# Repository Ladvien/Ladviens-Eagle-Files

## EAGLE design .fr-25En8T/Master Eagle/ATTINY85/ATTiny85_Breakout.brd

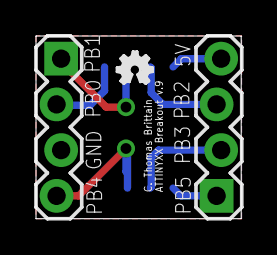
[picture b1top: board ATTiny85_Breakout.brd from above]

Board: 2 copper layers, 11.4 x 10.2 mm, 4 parts (1 on the bottom side), 8 nets.

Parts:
JP1, JP2: 1X04_LOCK
U$1: ATTINY45; SO08-EIAJ
U$2: OSHW_FILLX70_NOTEXT

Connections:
GND: JP2.3, U$1.4
PB0: JP2.2, U$1.5
PB1: JP2.1, U$1.6
PB2: JP1.3, U$1.7
PB3: JP1.2, U$1.2
PB4: JP2.4, U$1.3
PB5: JP1.1, U$1.1
VCC: JP1.4, U$1.8

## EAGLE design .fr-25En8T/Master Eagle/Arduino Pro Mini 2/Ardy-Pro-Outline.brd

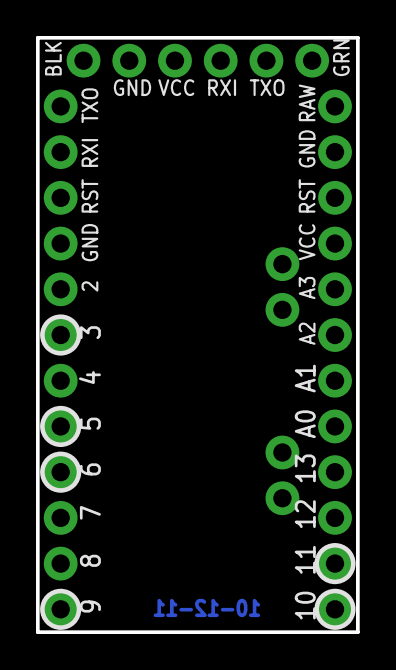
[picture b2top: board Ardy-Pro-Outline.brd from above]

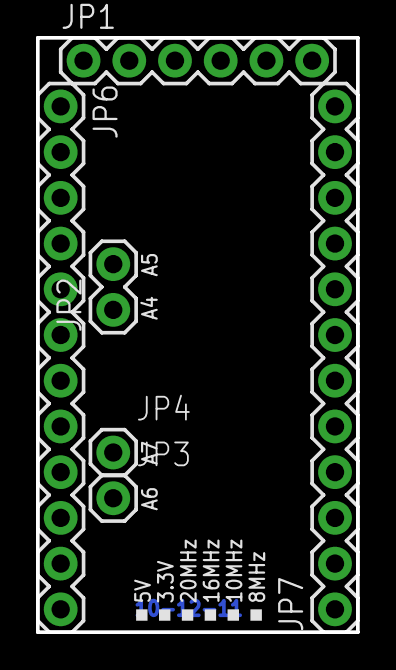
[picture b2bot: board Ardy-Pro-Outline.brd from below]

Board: 2 copper layers, 17.8 x 33.0 mm, 6 parts (6 on the bottom side), 5 nets, no tracks yet.

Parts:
JP1: FTDI Basic; 1X06
JP2: 1X02
JP3, JP4: 1X01
JP6, JP7: 1X12

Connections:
GND: JP1.5, JP1.6, JP6.2, JP7.9
RESET: JP6.3, JP7.10
RXI: JP1.3, JP7.11
TXO: JP1.2, JP7.12
VCC: JP1.4, JP6.4

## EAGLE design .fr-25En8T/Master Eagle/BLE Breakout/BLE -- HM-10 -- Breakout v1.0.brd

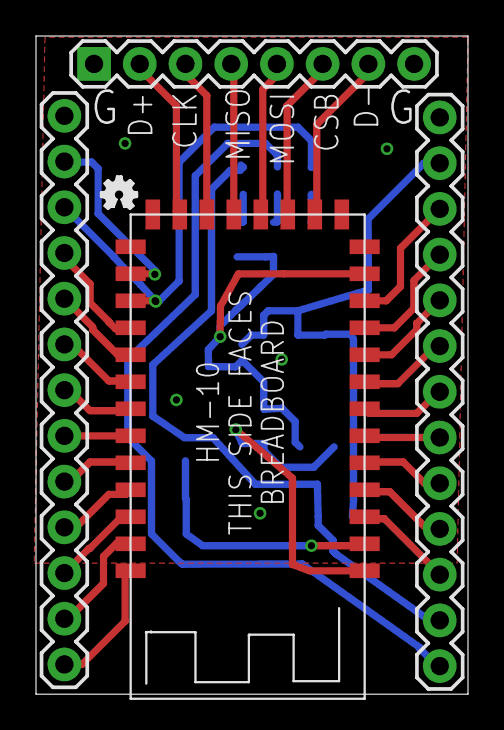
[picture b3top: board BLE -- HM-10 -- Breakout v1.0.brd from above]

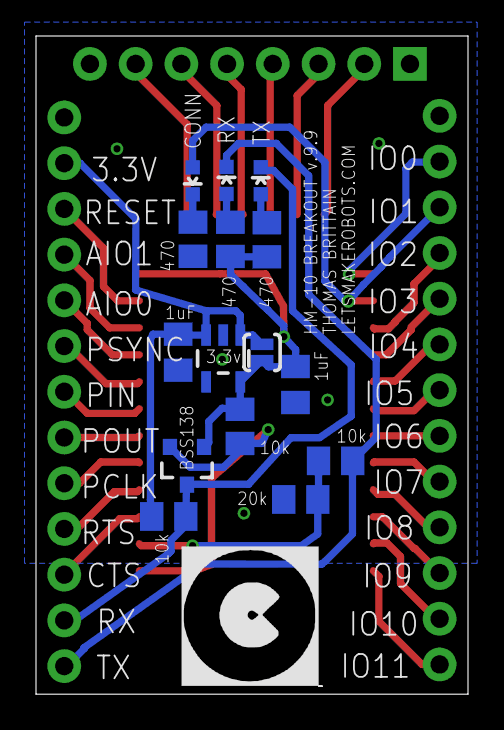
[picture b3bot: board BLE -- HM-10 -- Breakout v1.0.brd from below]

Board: 2 copper layers, 24.0 x 36.6 mm, 20 parts (15 on the bottom side), 37 nets.

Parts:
BSS138: MOSFET-NCHANNELSMD; SOT23-3
C1, C2: 1uF; C0805K
CONN_LED: LED-0603
JP1, JP2: M13; 1X13
JP3: 1X08
R1, R2: 1k; M0805
R3, R5, R6: 10k; M0805
R4: 20k; M0805
R7: 220; M0805
RX_LED: LED-0603
SJ1: SOLDERJUMPERNO; SJ_2S-NO
TX_LED: LED-0603
U1: V_REG_LDOSMD; SOT23-5
U$1: BLE-HM-10
U$3: OSHW_FILLX70_NOTEXT

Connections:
3_3V: BSS138.1, C2.1, R1.2, R2.2, R6.2, SJ1.1, U1.5, U$1.3.3V
5V: C1.1, JP1.2, R5.2, SJ1.2, U1.1, U1.3
GND: C1.2, C2.2, JP1.1, JP2.13, JP3.1, JP3.8, R4.2, R7.1, U1.2, U$1.GND1, U$1.GND2, U$1.GND3, U$1.GND4
HVTX->LVRX: R3.2, R4.1, U$1.UART_RX
LVRX->HVTX: BSS138.2, R6.1, U$1.UART_TX
unnamed: CONN_LED.A, JP2.11, U$1.PIO1
unnamed: JP1.3, U$1.RESET
unnamed: JP1.4, U$1.AIO1
unnamed: JP1.5, U$1.AIO0
unnamed: JP1.6, U$1.PCM_SYNC
unnamed: JP1.7, U$1.PCM_IN
unnamed: JP1.8, U$1.PCM_OUT
unnamed: JP1.9, U$1.PCM_CLK
unnamed: JP1.10, U$1.UART_RTS
unnamed: JP1.11, U$1.UART_CTS
unnamed: JP2.1, U$1.PIO11
unnamed: JP2.2, U$1.PIO10
unnamed: JP2.3, U$1.PIO9
unnamed: JP2.4, U$1.PIO8
unnamed: JP2.5, U$1.PIO7
unnamed: JP2.6, U$1.PIO6
unnamed: JP2.7, U$1.PIO5
unnamed: JP2.8, U$1.PIO4
unnamed: JP2.9, U$1.PIO3
unnamed: JP2.10, U$1.PIO2
unnamed: R1.1, TX_LED.A
unnamed: JP2.12, U$1.PIO0
unnamed: CONN_LED.C, R7.2
unnamed: R2.1, RX_LED.A
unnamed: JP3.2, U$1.USB_D+
unnamed: JP3.3, U$1.SPI_CLK
unnamed: JP3.4, U$1.SPI_MISO
unnamed: JP3.5, U$1.SPI_MOSI
unnamed: JP3.6, U$1.SPI_CSB
unnamed: JP3.7, U$1.USB_D-
RX: JP1.13, R3.1, RX_LED.C
TX: BSS138.3, JP1.12, R5.1, TX_LED.C

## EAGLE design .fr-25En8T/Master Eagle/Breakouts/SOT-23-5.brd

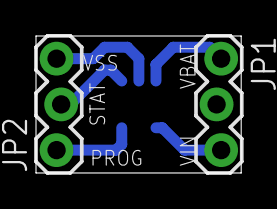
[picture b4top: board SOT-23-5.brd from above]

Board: 2 copper layers, 11.4 x 7.6 mm, 3 parts (1 on the bottom side), 5 nets.

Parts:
JP1, JP2: 1X03_LOCK
U1: MCP73831; SOT23-5

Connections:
PROG: JP2.1, U1.5
STAT: JP2.2, U1.1
VBAT: JP1.1, U1.3
VIN: JP1.3, U1.4
VSS: JP2.3, U1.2

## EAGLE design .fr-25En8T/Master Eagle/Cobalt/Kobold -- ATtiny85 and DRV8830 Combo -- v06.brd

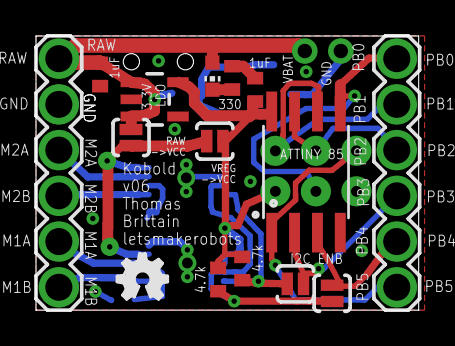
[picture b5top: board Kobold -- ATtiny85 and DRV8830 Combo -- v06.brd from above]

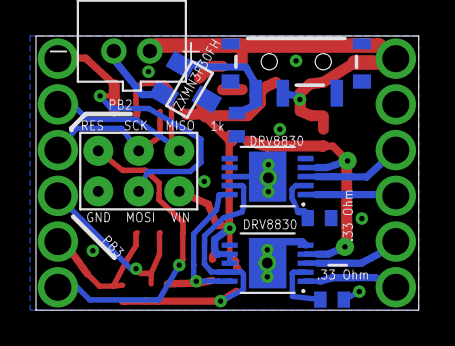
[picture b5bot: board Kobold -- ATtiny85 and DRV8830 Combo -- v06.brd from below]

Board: 2 copper layers, 21.3 x 15.2 mm, 24 parts (9 on the bottom side), 21 nets.

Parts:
1K: R3; R0402
BATTERY: JST-PH-2-THM
C1, C2: 1uf; C0402
LED1: CHIP-LED0603
R1, R3: .33; R0402
R2, R4: 1k; R0402
R5: 330; R0402
RAW: SOLDERJUMPERNO; SJ_2S-NO
S1: SWITCH-SPST-SMD-A
SJ6, SJ7: SOLDERJUMPERNO; SJ_2S-NO
U1: V_REG_LDOSMD; SOT23-5
U2, U3: DRV8830; MSOP-10-GNDPAD
U$1, U$4: 1X6_SHORT_ROUND
U$2: ATTINY85; SO08-EIAJ
U$5: POGO_PIN_SPI_PAD
U$6: OSHW_FILLX100_NOTEXT
VREG: SOLDERJUMPERNO; SJ_2S-NO
ZXMN3F30FH: MOSFET-NCHANNELBSS123LT1G; SOT23

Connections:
BAT_GND: BATTERY.2, ZXMN3F30FH.2
BAT_RAW: BATTERY.1, C1.1, LED1.A, RAW.1, S1.2, U1.1, U1.3, U$4.1
GND: C1.2, C2.2, R1.1, R3.1, R4.1, R5.2, U1.2, U2.5, U2.GND, U3.5, U3.7, U3.8, U3.GND, U$2.4, U$4.2, U$5.GND, ZXMN3F30FH.3
M1_A: U2.3, U$4.5
M1_B: U2.1, U$4.6
M2_A: U3.3, U$4.3
M2_B: U3.1, U$4.4
unnamed: R1.2, U3.2
unnamed: R3.2, U2.2
unnamed: LED1.C, R5.1
unnamed: R4.2, S1.1, ZXMN3F30FH.1
PB0: U$1.1, U$2.5, U$5.MOSI
PB1: U$1.2, U$2.6, U$5.MISO
PB2: U$1.3, U$2.7, U$5.SCK
PB3: SJ7.2, U$1.4, U$2.2
PB4: SJ6.2, U$1.5, U$2.3
PB5: U$1.6, U$2.1, U$5.RST
SCL: R2.2, SJ7.1, U2.10, U3.10
SDA: 1K.2, SJ6.1, U2.9, U3.9
VCC: RAW.2, U2.4, U3.4, VREG.2
VREG: 1K.1, C2.1, R2.1, U1.5, U2.7, U2.8, U$2.8, U$5.VCC, VREG.1

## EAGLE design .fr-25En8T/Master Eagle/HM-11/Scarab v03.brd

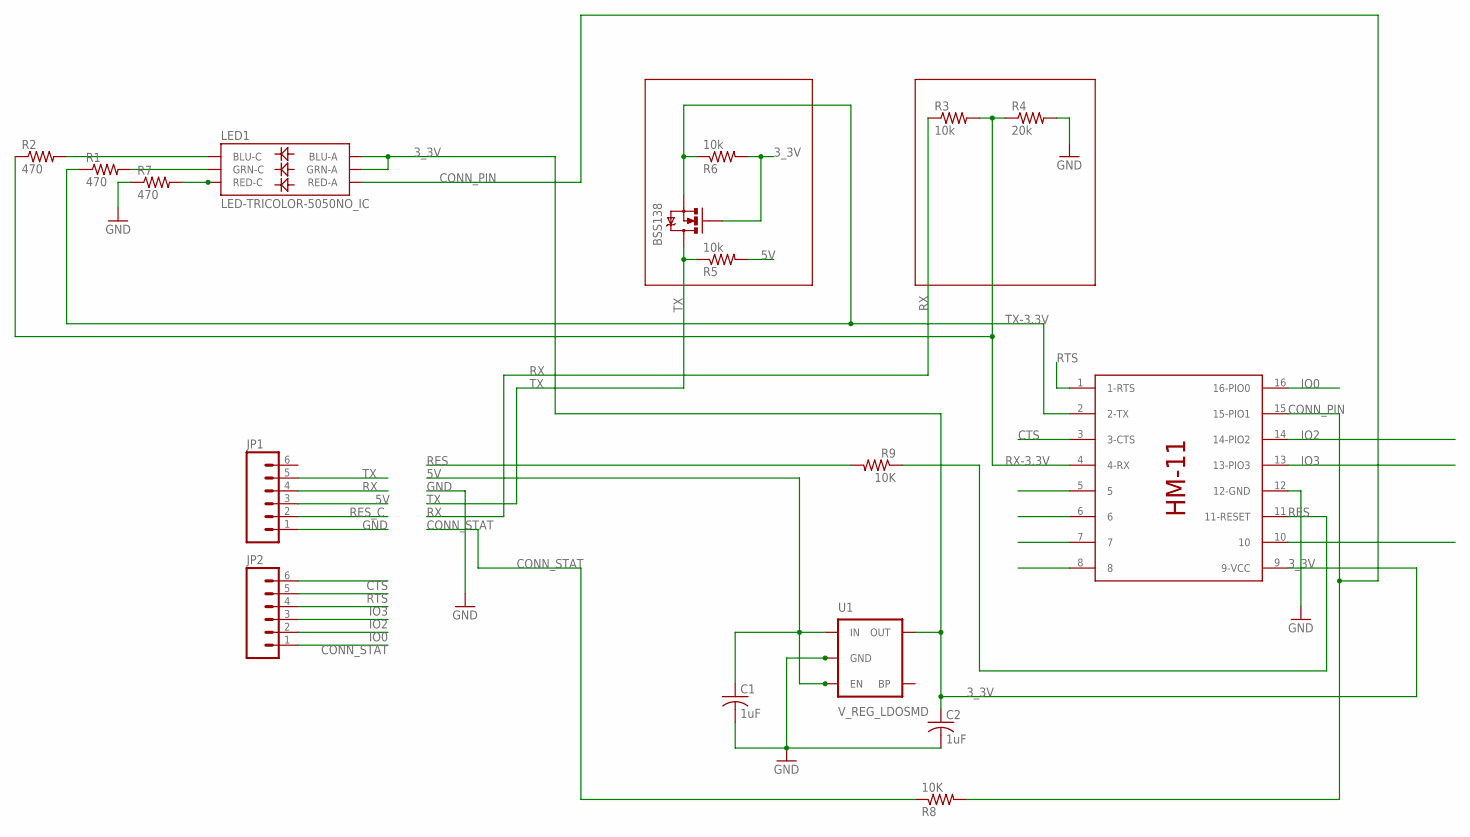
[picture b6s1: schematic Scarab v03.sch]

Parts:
BSS138: MOSFET-NCHANNELSMD; SOT23-3
C1, C2: 1uF; C0402
JP1, JP2: M06LOCK; 1X06_LOCK
LED1: LED-TRICOLOR-5050NO_IC; LED-TRICOLOR-5050
R1, R2, R7: 470; R0402
R3, R5, R6: 10k; R0402
R4: 20k; R0402
R8, R9: 10K; R0402
U1: V_REG_LDOSMD; SOT23-5
U$1: HM-11

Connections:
3_3V: BSS138.1 (G), C2.1, LED1.1 (GRN-A), LED1.3 (BLU-A), R6.2, U1.5 (OUT), U$1.9 (9-VCC)
5V: C1.1, JP1.3, R5.2, U1.1 (IN), U1.3 (EN)
CONN_PIN: LED1.2 (RED-A), R8.2, U$1.15 (15-PIO1)
CONN_STAT: JP2.1, R8.1
CTS: JP2.6, U$1.3 (3-CTS)
GND: C1.2, C2.2, JP1.1, R4.2, R7.1, U1.2 (GND), U$1.12 (12-GND)
IO0: JP2.2, U$1.16 (16-PIO0)
IO2: JP2.3, U$1.14 (14-PIO2)
IO3: JP2.4, U$1.13 (13-PIO3)
unnamed: LED1.6 (GRN-C), R1.2
unnamed: LED1.4 (BLU-C), R2.2
unnamed: LED1.5 (RED-C), R7.2
RES: R9.1, U$1.11 (11-RESET)
RES_C: JP1.2, R9.2
RTS: JP2.5, U$1.1 (1-RTS)
RX: JP1.4, R3.1
RX-3.3V: R2.1, R3.2, R4.1, U$1.4 (4-RX)
TX: BSS138.3 (D), JP1.5, R5.1
TX-3.3V: BSS138.2 (S), R1.1, R6.1, U$1.2 (2-TX)

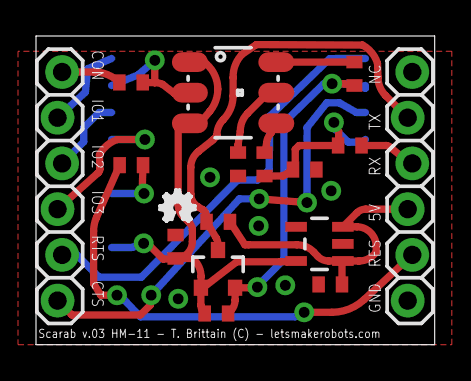
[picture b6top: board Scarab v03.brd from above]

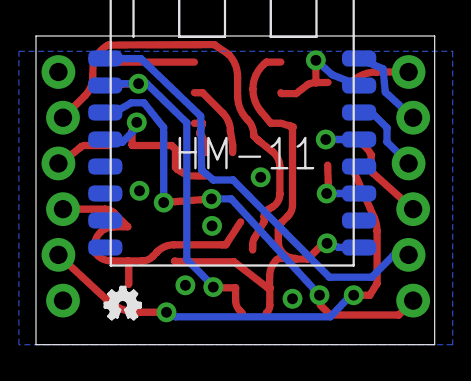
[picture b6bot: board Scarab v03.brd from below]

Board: 2 copper layers, 22.1 x 17.1 mm, 19 parts (2 on the bottom side), 19 nets.

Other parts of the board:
U$3, U$4: OSHW_FILLX70_NOTEXT

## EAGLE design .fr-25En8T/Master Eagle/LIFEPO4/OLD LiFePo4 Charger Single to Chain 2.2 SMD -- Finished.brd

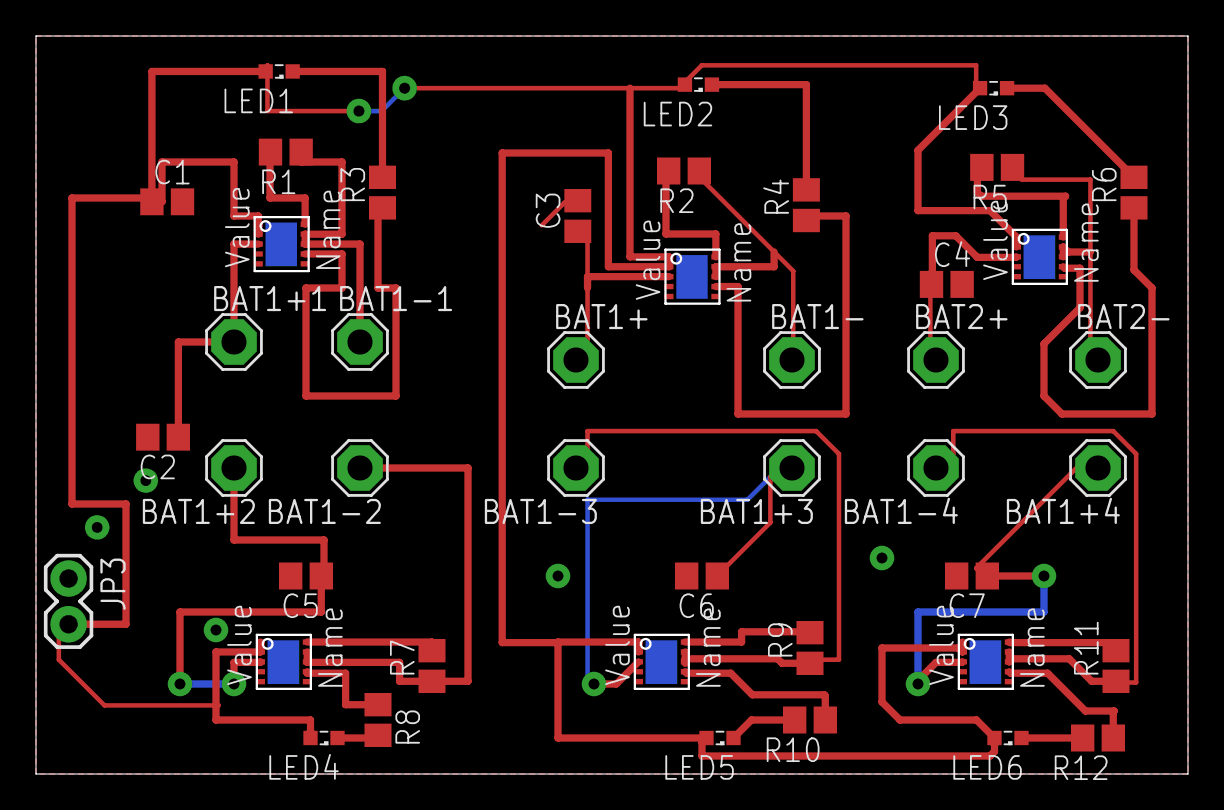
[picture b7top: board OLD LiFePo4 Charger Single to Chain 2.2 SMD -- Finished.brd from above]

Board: 2 copper layers, 64.0 x 41.0 mm, 44 parts (0 on the bottom side), 32 nets.

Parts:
BAT1+, BAT1+1, BAT1+2, BAT1+3, BAT1+4, BAT1-, BAT1-1, BAT1-2, BAT1-3, BAT1-4, BAT2+, BAT2-: SE14
C1, C2, C3, C4, C5, C6, C7: 4.7; C0805
JP3: Vraw/Grnd; 1X02
LED1, LED2, LED3, LED4, LED5, LED6: 3.2v; SML0603
R1, R2, R5, R7, R9, R11: 1.5k; R0805
R3, R4, R6, R8, R10, R12: 1k; R0805
U$1, U$2, U$3, U$5, U$6, U$8: MCP73123/223

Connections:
GND: C1.2, C2.2, C3.2, C4.2, C5.2, C6.2, C7.2, JP3.1
unnamed: C1.1, JP3.2, LED1.A, LED2.A, LED3.A, LED4.A, LED5.A, LED6.A, U$1.1, U$1.2, U$2.1, U$2.2, U$3.1, U$3.2, U$5.1, U$5.2, U$6.1, U$6.2, U$8.1, U$8.2
unnamed: BAT1+2.MP, C5.1, U$3.3
unnamed: BAT1+1.MP, C2.1, U$8.3
unnamed: R1.2, U$8.10
unnamed: BAT1-1.MP, R1.1, U$8.8, U$8.9
unnamed: LED1.C, R3.2
unnamed: R3.1, U$8.7
unnamed: BAT1+.MP, C3.1, U$1.3
unnamed: BAT1-.MP, R2.1, U$1.8, U$1.9
unnamed: R4.1, U$1.7
unnamed: R2.2, U$1.10
unnamed: BAT2+.MP, C4.1, U$2.3
unnamed: LED2.C, R4.2
unnamed: BAT2-.MP, R5.1, U$2.8, U$2.9
unnamed: R6.1, U$2.7
unnamed: R5.2, U$2.10
unnamed: LED3.C, R6.2
unnamed: BAT1-2.MP, R7.1, U$3.8, U$3.9
unnamed: R8.1, U$3.7
unnamed: R7.2, U$3.10
unnamed: LED4.C, R8.2
unnamed: BAT1+3.MP, C6.1, U$5.3
unnamed: BAT1-3.MP, R9.1, U$5.8, U$5.9
unnamed: R10.1, U$5.7
unnamed: R9.2, U$5.10
unnamed: LED5.C, R10.2
unnamed: BAT1+4.MP, C7.1, U$6.3
unnamed: BAT1-4.MP, R11.1, U$6.8, U$6.9
unnamed: R12.1, U$6.7
unnamed: R11.2, U$6.10
unnamed: LED6.C, R12.2

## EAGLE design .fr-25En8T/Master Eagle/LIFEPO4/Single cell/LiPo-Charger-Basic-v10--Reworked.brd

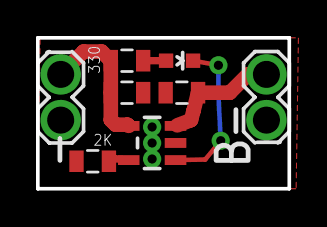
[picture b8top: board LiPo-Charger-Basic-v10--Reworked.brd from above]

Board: 2 copper layers, 14.0 x 8.4 mm, 9 parts (1 on the bottom side), 6 nets.

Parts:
C3, C4: 4.7uF; 0805
D11: RED; LED-0603
R3: 330; 0805
R4: 2K; 0805
U1: MCP73831; SOT23-5
U$1, U$4: 1X2_SHORT_ROUND
U$3: OSHW_FILLX100_NOTEXT

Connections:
GND: C3.2, C4.2, R4.2, U1.2, U$1.1, U$4.2
unnamed: D11.A, R3.1
PROG: R4.1, U1.5
STAT: D11.C, U1.1
VCC: C4.1, U1.3, U$4.1
VIN: C3.1, R3.2, U1.4, U$1.2

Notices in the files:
parts and their libraries:
SparkFun: Licensing: CC v3.0 Share-Alike You are welcome to use this library for commercial purposes.
SparkFun-Connectors: Licensing: Creative Commons ShareAlike 4.0 International - https://creativecommons.org/licenses/by-sa/4.0
